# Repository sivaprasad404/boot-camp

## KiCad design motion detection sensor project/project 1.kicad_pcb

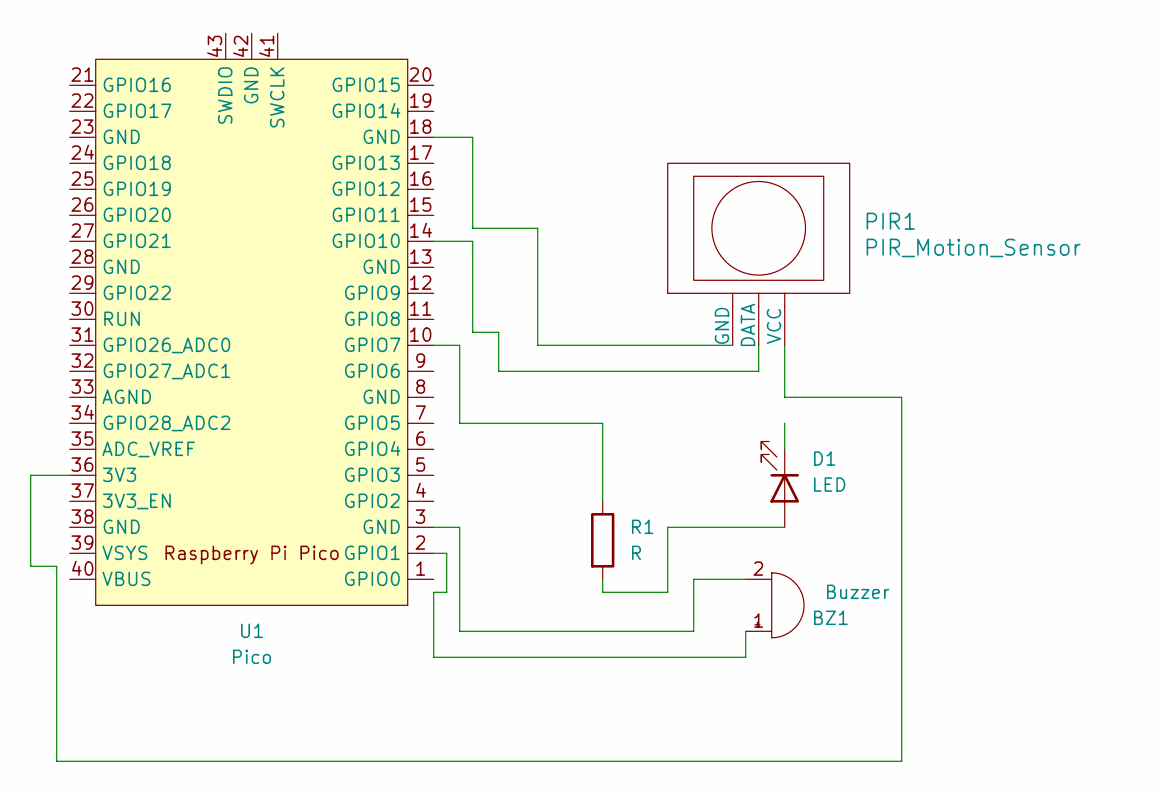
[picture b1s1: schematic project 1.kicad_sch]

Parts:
BZ1: Buzzer; Buzzer_12x9.5RM7.6
D1: LED; LED_D1.8mm_W1.8mm_H2.4mm_Horizontal_O1.27mm_Z1.6mm
PIR1: PIR_Motion_Sensor; InvenSense_QFN-24_3x3mm_P0.4mm
R1: R; R_Array_SIP4
U1: Pico; RPi_Pico_SMD_TH

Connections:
unnamed: BZ1.1 (+), U1.2 (GPIO1)
unnamed: BZ1.2 (-), U1.3 (GND)
unnamed: D1.2 (A), R1.2
unnamed: PIR1.2 (DATA), U1.14 (GPIO10)
unnamed: PIR1.1 (GND), U1.18 (GND)
unnamed: PIR1.3 (VCC), U1.36 (3V3)
unnamed: R1.1, U1.10 (GPIO7)

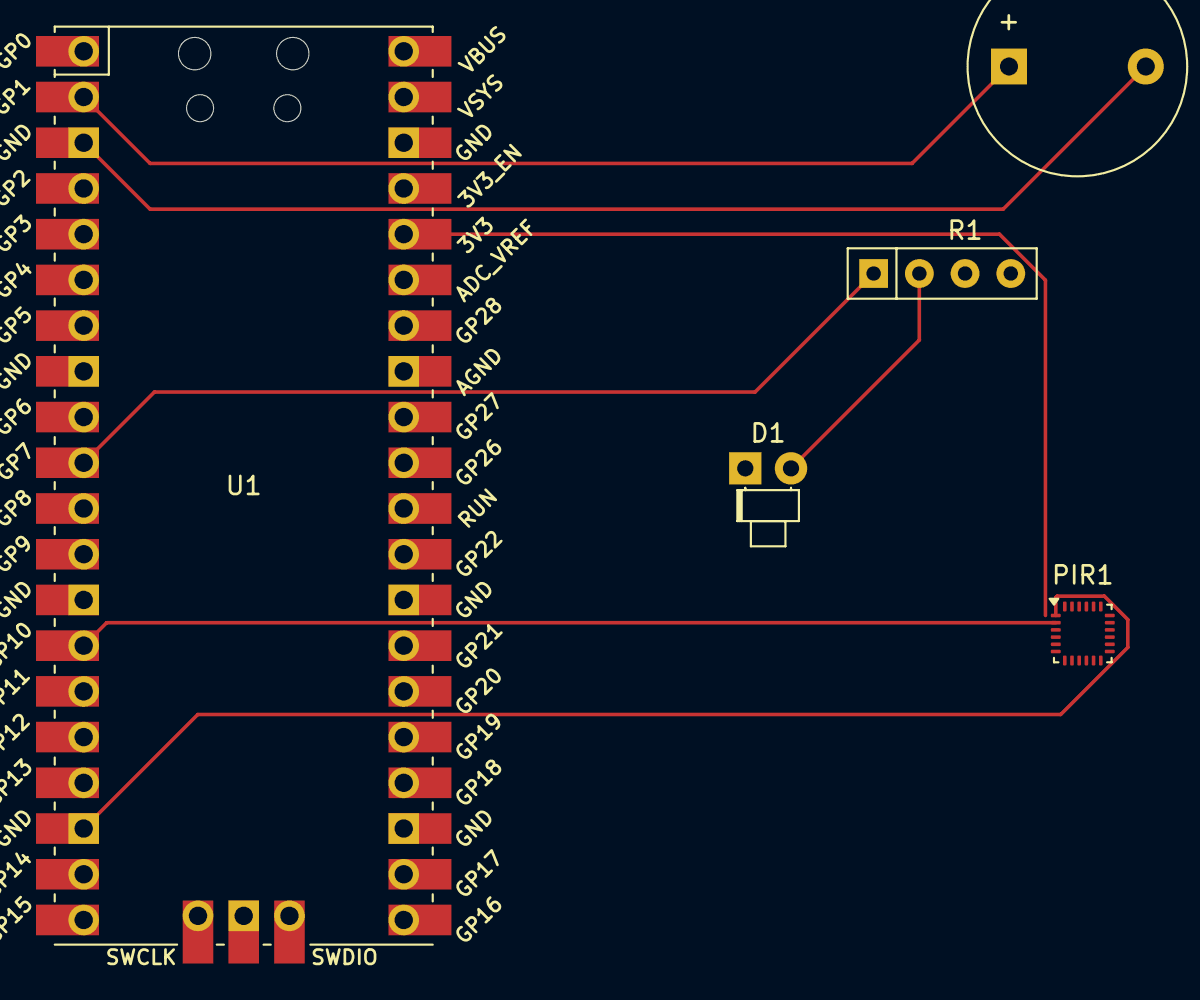
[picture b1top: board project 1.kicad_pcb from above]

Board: 2 copper layers, 5 parts (0 on the bottom side), 7 nets.
